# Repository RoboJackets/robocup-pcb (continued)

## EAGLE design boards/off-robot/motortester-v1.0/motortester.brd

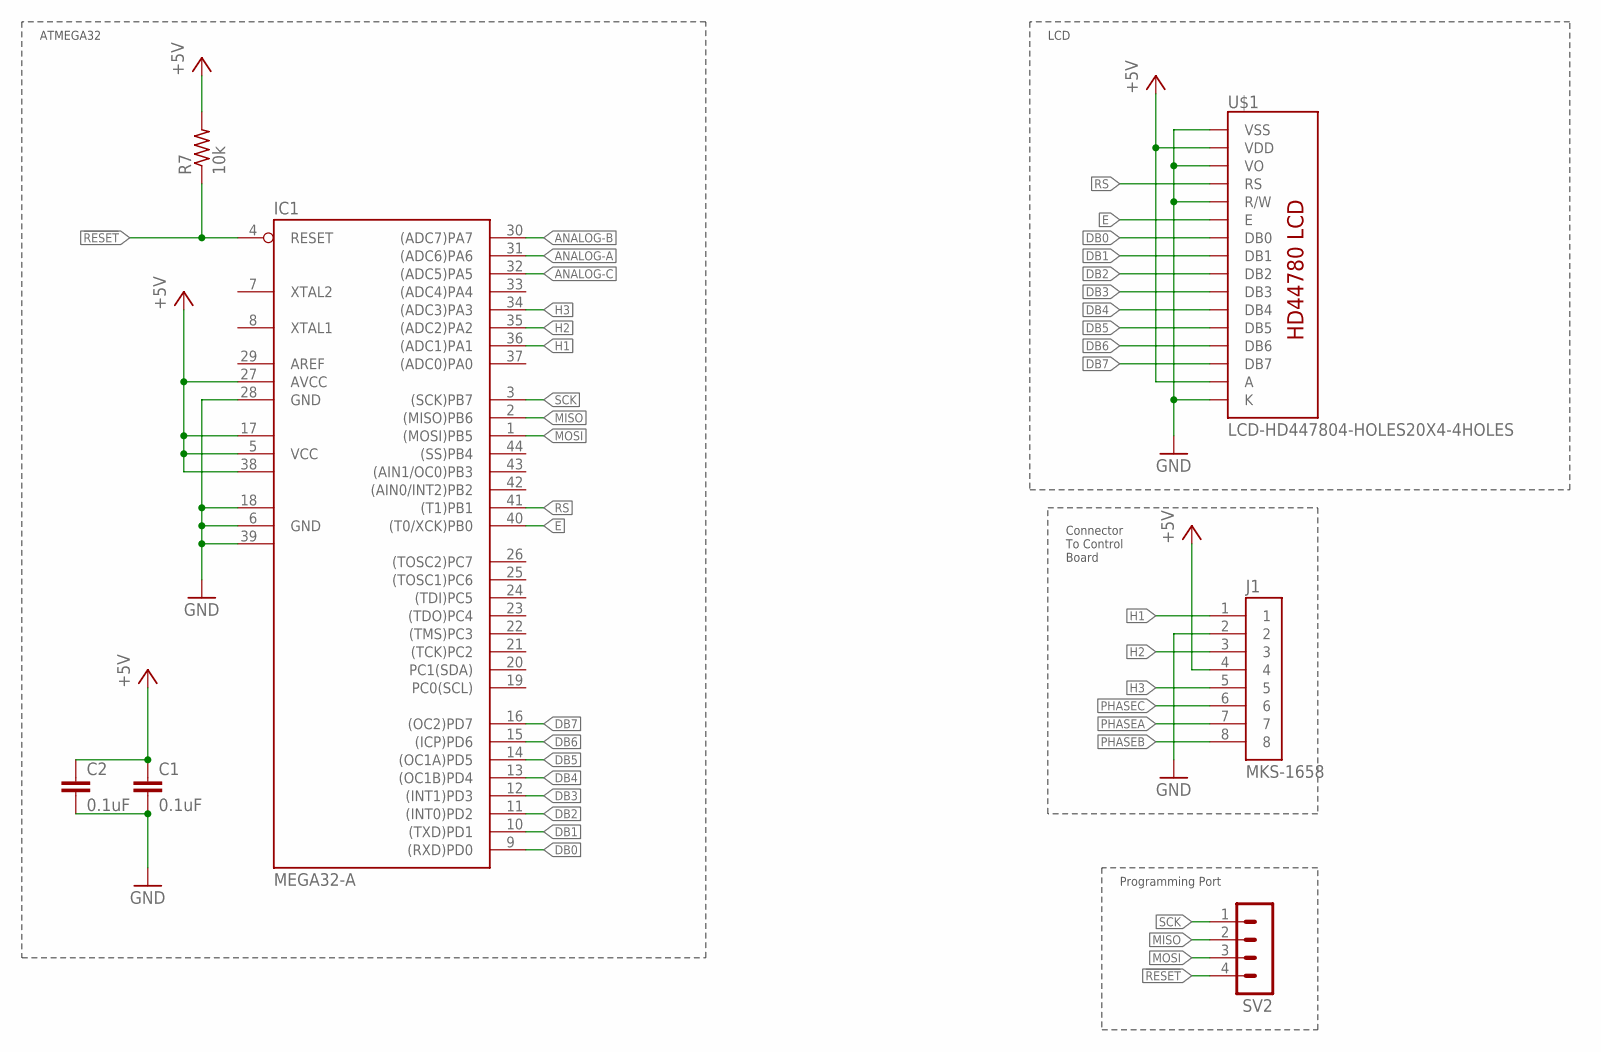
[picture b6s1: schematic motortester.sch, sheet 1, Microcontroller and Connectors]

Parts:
C1, C2: 0.1uF; C0603
IC1: MEGA32-A; TQFP44
J1: MKS-1658
R7: 10k; R0603
SV2: MA04-1
U$1: LCD-HD447804-HOLES20X4-4HOLES; LCD-20X4-4HOLES

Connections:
!RESET!: IC1.4 (RESET), R7.1, SV2.4
ANALOG-A: IC1.31 ((ADC6)PA6); also elsewhere on the board
ANALOG-B: IC1.30 ((ADC7)PA7); also elsewhere on the board
ANALOG-C: IC1.32 ((ADC5)PA5); also elsewhere on the board
DB0: IC1.9 ((RXD)PD0), U$1.P$7 (DB0)
DB1: IC1.10 ((TXD)PD1), U$1.P$8 (DB1)
DB2: IC1.11 ((INT0)PD2), U$1.P$9 (DB2)
DB3: IC1.12 ((INT1)PD3), U$1.P$10 (DB3)
DB4: IC1.13 ((OC1B)PD4), U$1.P$11 (DB4)
DB5: IC1.14 ((OC1A)PD5), U$1.P$12 (DB5)
DB6: IC1.15 ((ICP)PD6), U$1.P$13 (DB6)
DB7: IC1.16 ((OC2)PD7), U$1.P$14 (DB7)
E: IC1.40 ((T0/XCK)PB0), U$1.P$6 (E)
GND: C1.2, C2.2, IC1.6 (GND), IC1.18 (GND1), IC1.28 (GND), IC1.39 (GND2), J1.2, U$1.P$1 (VSS), U$1.P$3 (VO), U$1.P$5 (R/W), U$1.P$16 (K)
H1: IC1.36 ((ADC1)PA1), J1.1
H2: IC1.35 ((ADC2)PA2), J1.3
H3: IC1.34 ((ADC3)PA3), J1.5
MISO: IC1.2 ((MISO)PB6), SV2.2
MOSI: IC1.1 ((MOSI)PB5), SV2.3
PHASEA: J1.7; also elsewhere on the board
PHASEB: J1.8; also elsewhere on the board
PHASEC: J1.6; also elsewhere on the board
RS: IC1.41 ((T1)PB1), U$1.P$4 (RS)
SCK: IC1.3 ((SCK)PB7), SV2.1
VCC: C1.1, C2.1, IC1.5 (VCC), IC1.17 (VCC1), IC1.27 (AVCC), IC1.38 (VCC2), J1.4, R7.2, U$1.P$2 (VDD), U$1.P$15 (A)

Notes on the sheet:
ATMEGA32
LCD
Connector To Control Board
Programming Port

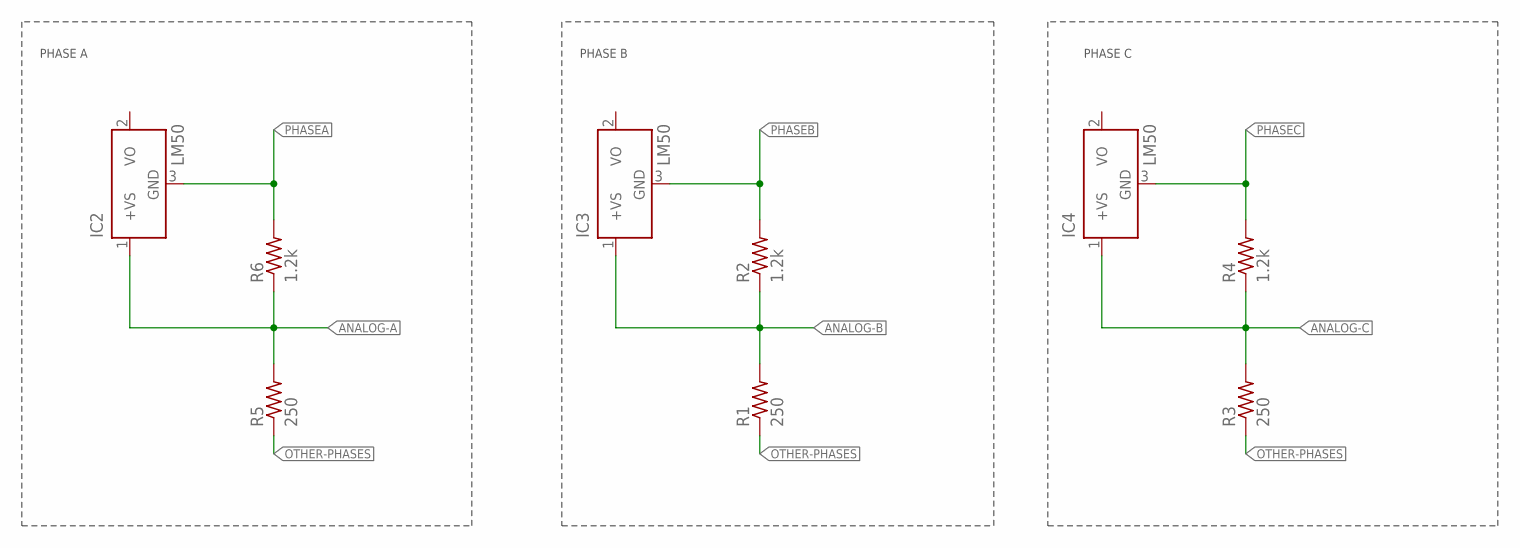
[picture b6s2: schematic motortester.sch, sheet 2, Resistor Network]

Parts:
IC2, IC3, IC4: LM50; SOT23
R1, R3, R5: 250; R0603
R2, R4, R6: 1.2k; R0603

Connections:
ANALOG-A: IC2.1 (+VS), R5.2, R6.1; also elsewhere on the board
ANALOG-B: IC3.1 (+VS), R1.2, R2.1; also elsewhere on the board
ANALOG-C: IC4.1 (+VS), R3.2, R4.1; also elsewhere on the board
OTHER-PHASES: R1.1, R3.1, R5.1
PHASEA: IC2.3 (GND), R6.2; also elsewhere on the board
PHASEB: IC3.3 (GND), R2.2; also elsewhere on the board
PHASEC: IC4.3 (GND), R4.2; also elsewhere on the board

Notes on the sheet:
PHASE A
PHASE B
PHASE C

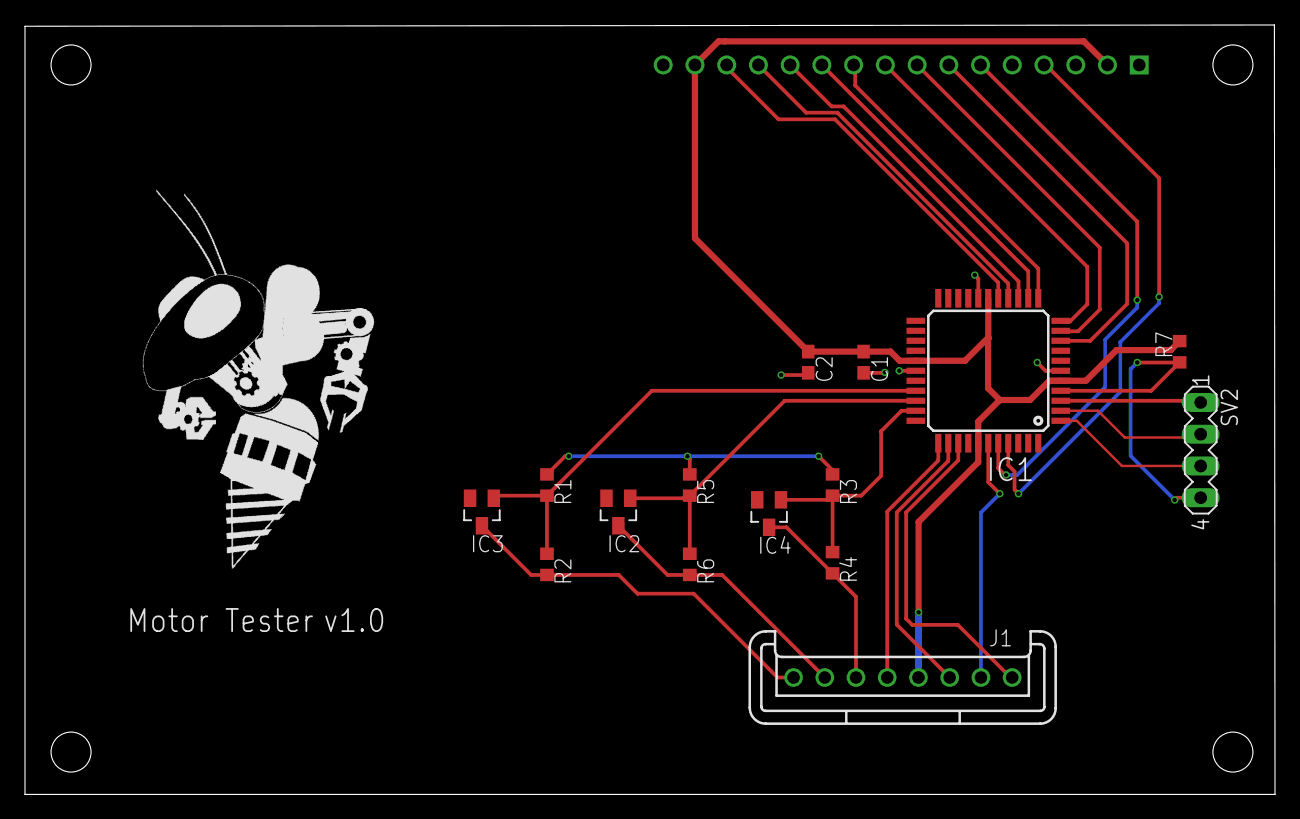
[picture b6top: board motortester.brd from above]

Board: 2 copper layers, 100.1 x 61.6 mm, 17 parts (1 on the bottom side), 26 nets.

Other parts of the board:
U$2: ROBOBUZZ_1.4X

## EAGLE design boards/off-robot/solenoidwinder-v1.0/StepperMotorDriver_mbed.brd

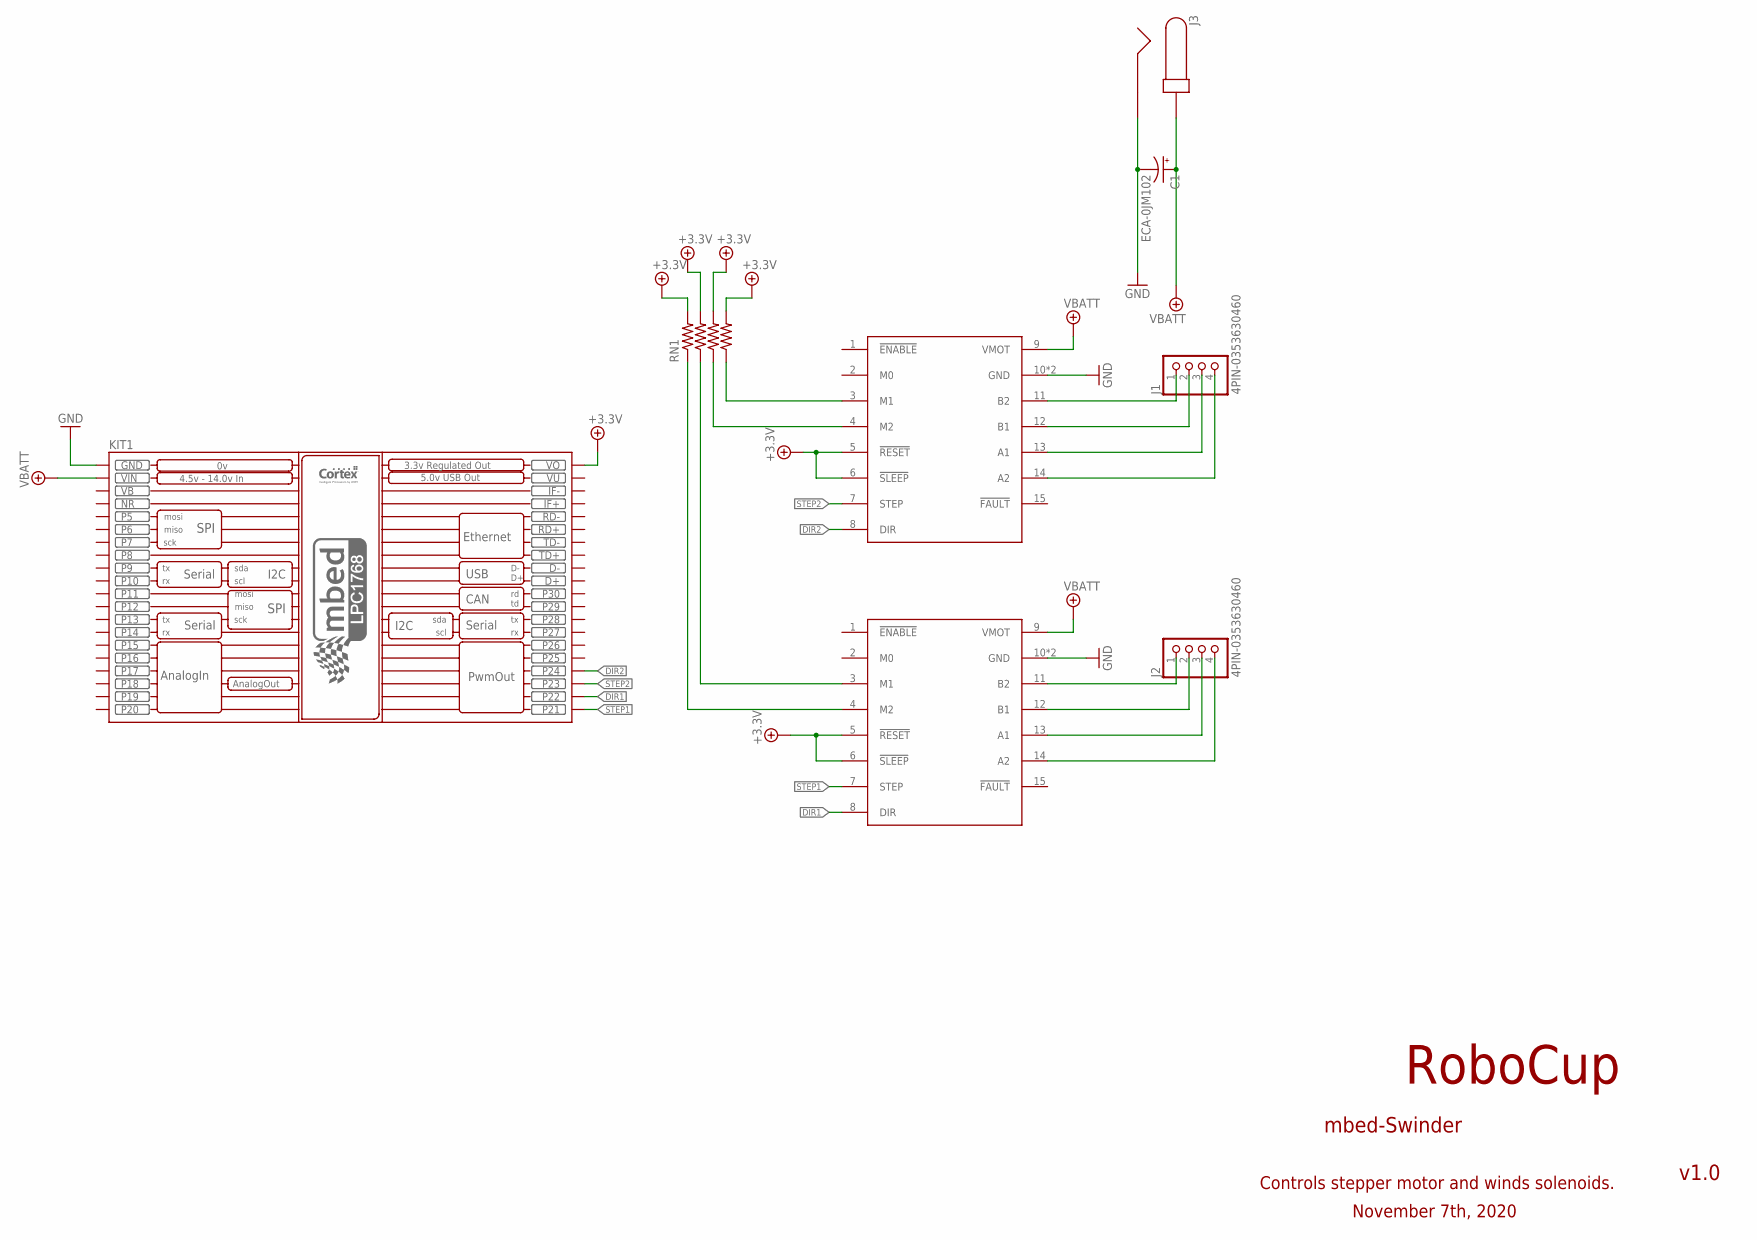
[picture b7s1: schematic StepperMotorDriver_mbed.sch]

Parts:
C1: ECA-0JM102; PCAP_8X112
J1, J2: 4PIN-0353630460; 0353630460
J3: PJ-037A
KIT1: MBED_NXP_LPC1768; MBED-KIT
RN1: RA-41206; RA-4_1206
U$1, U$2: DRV8825

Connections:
+3.3V: KIT1.VOUT (VO), RN1.2, RN1.4, RN1.6, RN1.8, U$1.5 (!RESET!), U$1.6 (!SLEEP!), U$2.5 (!RESET!), U$2.6 (!SLEEP!)
DIR1: KIT1.P$22 (P22), U$1.8 (DIR)
DIR2: KIT1.P$24 (P24), U$2.8 (DIR)
GND: C1.2 (-), J3.P$1 (2), KIT1.GND, U$1.10 (GND), U$1.16 (GND), U$2.10 (GND), U$2.16 (GND); also elsewhere on the board
unnamed: J1.1, U$2.11 (B2)
unnamed: J1.2, U$2.12 (B1)
unnamed: J1.3, U$2.13 (A1)
unnamed: J1.4, U$2.14 (A2)
unnamed: J2.1, U$1.11 (B2)
unnamed: J2.2, U$1.12 (B1)
unnamed: J2.3, U$1.13 (A1)
unnamed: J2.4, U$1.14 (A2)
unnamed: RN1.7, U$2.3 (M1)
unnamed: RN1.5, U$2.4 (M2)
unnamed: RN1.3, U$1.3 (M1)
unnamed: RN1.1, U$1.4 (M2)
STEP1: KIT1.P$21 (P21), U$1.7 (STEP)
STEP2: KIT1.P$23 (P23), U$2.7 (STEP)
VB: KIT1.VB
VBATT: C1.1 (+), J3.P$2 (1), KIT1.VIN, U$1.9 (VMOT), U$2.9 (VMOT)
VU: KIT1.VU

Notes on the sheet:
RoboCup
mbed-Swinder
v1.0
Controls stepper motor and winds solenoids.
November 7th, 2020

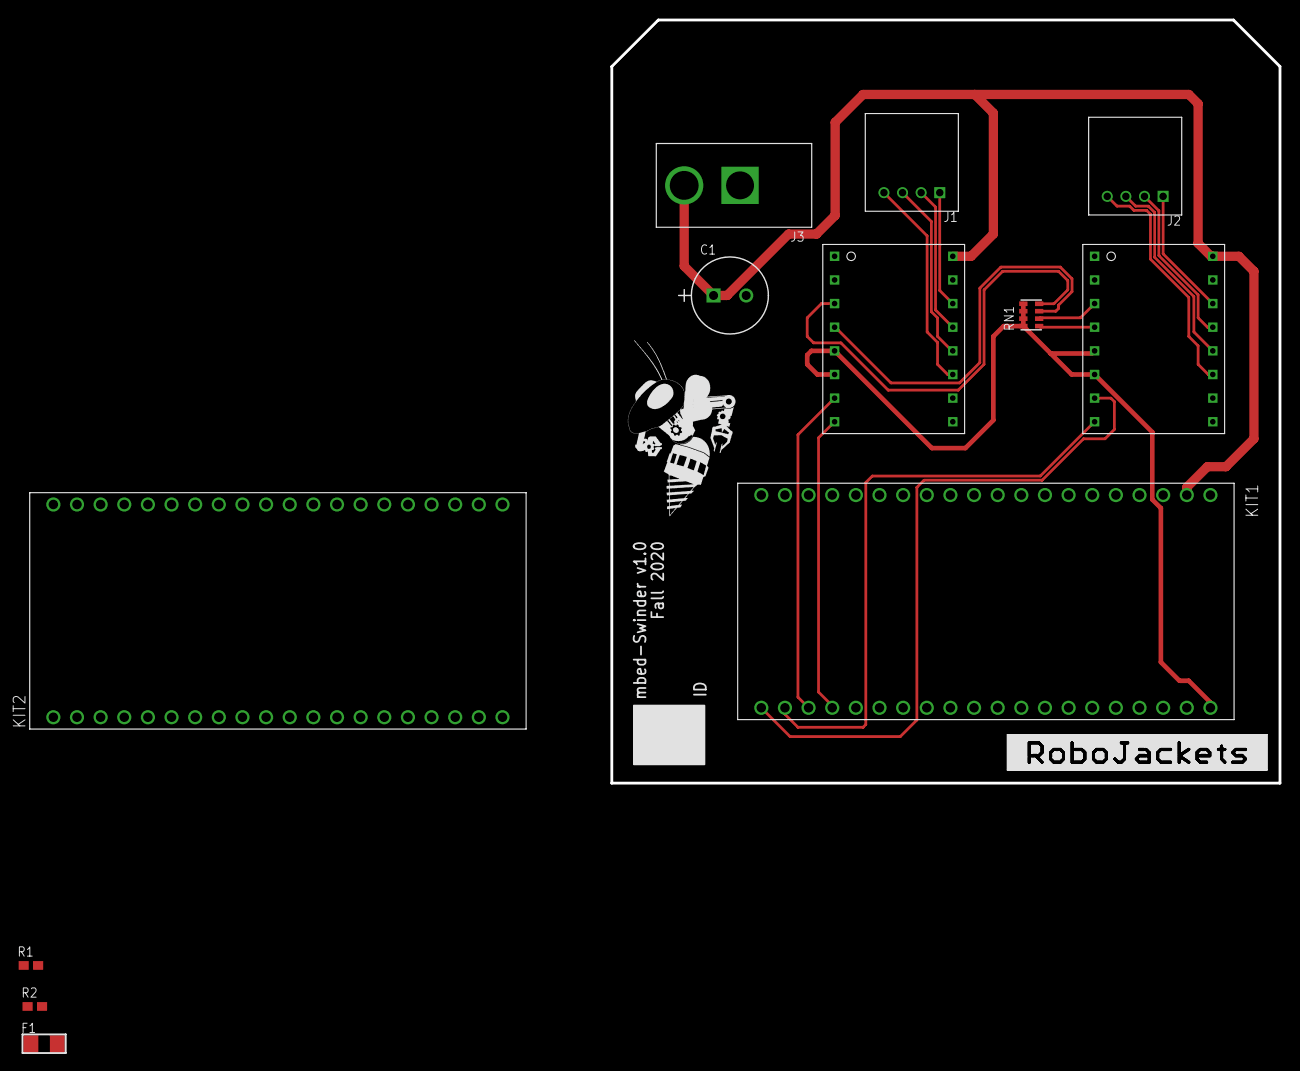
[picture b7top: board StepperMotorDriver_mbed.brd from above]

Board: 2 copper layers, 71.8 x 82.0 mm, 14 parts (0 on the bottom side), 19 nets.

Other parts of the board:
F1: F1206
KIT2: MTRAIN; MTRAIN-KIT
R1, R2: R0603W
U$4: ROBOJACKETS
U$5: ROBOBUZZ_1.0X

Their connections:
GND: KIT2.GND; also elsewhere on the board
